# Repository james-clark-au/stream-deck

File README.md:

# James Neko's Stream Deck

I made my own 6-key macropad for streaming out of an old mechanical key 'switch tester' I had! In doing so, I designed and had my very first PCB manufactured!

There's code here for both Arduino C++ _(Using a Nano, and relying on a Perl [lazy-serial-daemon](https://github.com/james-clark-au/lazy-serial-daemon) plugin to respond to the keys)_ and CircuitPython for a TENSTAR RP2040 board that uses the Pro Micro form factor.

There's also some 3D printing files - one for the partial enclosure I adapted my switch tester with, one for a full housing for it.

## Configuration

Presuming you're using the RP2040 / CircuitPython version, you might want some help on configuring it.

### Getting the CIRCUITPY drive to show up

Because it's a bit annoying to see the virtual USB drive show up all the time, I configure mine to hide it by default. This is done by editing `boot.py` and changing the line `HIDE_CIRCUITPY_DRIVE = False` to `True`. When this is set to `True`, the device will only show up as two USB Serial ports and one USB HID (Keyboard/Mouse) device.

To get it to show up as a USB Mass Storage device again, so you can edit the onboard files, hold down Key 0 - the one closest to the cable - as you plug it in. You can let go once the drive shows up.

On the CIRCUITPY drive, the two files you want to edit are `boot.py` for the setting above, and `code.py` to change your keys' behaviours. If you're on a Microsoft system you _might_ need a text editor smarter than NOTEPAD.EXE.

### Editing the key mapping

At the top of `code.py` you should see the current behaviours assigned to each key. The example configuration defines two modes that can be switched between:-

```python
config_mode0 = {
  0: RadioButton(key=(Keycode.GUI, Keycode.Q), group=(0, 1, 2)),
  1: RadioButton(key=(Keycode.GUI, Keycode.R), group=(0, 1, 2)),
  2: RadioButton(key=(Keycode.GUI, Keycode.S), group=(0, 1, 2)),
  3: SimpleButton(key=Keycode.RIGHT_SHIFT),
  4: SpamButton(key=MouseLeft(), delay_ms=30),
  5: ModeSwitch(),
}
config_mode1 = {
  0: RadioButtonWithHold(key=(Keycode.CONTROL, Keycode.ALT, Keycode.SHIFT, Keycode.ONE), key_when_held="Hello", group=(0, 1)),
  1: RadioButtonWithHold(key=(Keycode.CONTROL, Keycode.ALT, Keycode.SHIFT, Keycode.TWO), key_when_held="World", group=(0, 1)),
  2: MomentaryButton(key_on=(Keycode.GUI, Keycode.V), key_off=(Keycode.GUI, Keycode.V), led_initial=False),
  3: ToggleButton(key_on=(Keycode.GUI, Keycode.V), key_off=(Keycode.GUI, Keycode.V), led_initial=True),
  4: ToggleButton(key_on="Bed goes up", key_off="Bed goes down"),
  5: ModeSwitch(),
}
```

Slightly below that, those 'modes' are loaded with the line:-
```
deck = StreamDeck(lazy, [config_mode0, config_mode1])
```

You'll only need to modify that if you want to play with lots of different modes; if you just want the same behaviour for each key all the time, edit `config_mode0` and don't worry about anything else.

You'll see that after each key number 0..5 is the name of a Python class and some parameters in parentheses. Don't forget the comma at the end. The parameters change depending on which class you use, but most take a `key=` parameter, or two `key_on=` and `key_off=` parameters. The key can be defined in a few different ways, but more on that later.

Here are the different behaviours you can use (defined in `Behaviours.py`):-

#### SimpleButton(key=, light_while_pressed=True)

The most basic. Sends the key down event for your `key` when you press the button, sends the key up event when you release it.

`light_while_pressed` controls what the LED should do - turn on as you press the button (True), or be on all the time (False).

#### ToggleButton(key_on=, key_off=, led_initial=False)

This button remembers whether it's 'on' or 'off', and starts 'off' (`led_initial`).

It does a quick tap of `key_on` when you turn it on, and a quick tap of `key_off` (which can be the same as `key_on`) when you push the button and turn the LED off.

You could use this for e.g. a 'mute mic' button, so the LED indicates whether you've muted or unmuted it -- assuming it starts in the right state. If you want it to accurately reflect your mute state, you'd need to write extra code for your computer.

#### MomentaryButton(key_on=, key_off=, led_initial=False)

This button defaults to being 'on' or 'off' (depending on how you set `led_initial`), and becomes 'off' or 'on' only while held down.

Like the ToggleButton, it does a quick tap of `key_on` when you turn it on, and a quick tap of `key_off` (which can be the same as `key_on`) when you push the button and turn the LED off.

You could use this for e.g. a 'push to talk' button, or a 'push to mute' button, so that it sends the keyboard shortcut to mute/unmute when you start holding it, and does the same thing when you release it.

#### RadioButton(key=, group=())

This button works a little like the SimpleButton, sending a key down event when you push it and sending the key release event when you let go. What changes here is the LED - it starts off, and when it is pushed it switches itself on - and all the other RadioButtons in the same group off.

You could use this for switching scenes in OBS - set the `key=` for each button to some complicated shortcut key you set in OBS, and now as you switch between them, the relevant light will stay on! Be sure to set the `group=` parameter to the numbers of each other RadioButton - e.g. the whole deck would be `group=(0,1,2,3,4,5)`.

You _can_ make the LEDs update if you switch scenes from clicking around in OBS, but that will require a program running on your computer to connect to OBS and the USB Serial Port the Deck exposes.

#### RadioButtonWithHold(key=, key_when_held=, group=())

Exactly the same as RadioButton, but:-

- It only taps the `key` when released, if you tap the button.
- If you hold the button down longer than a second, it instead taps the `key_when_held`, and begins flashing its LED instead of the LED being on continuously.

This way you get an extra second layer of possible radio buttons!

#### SpamButton(key=, light_while_pressed=True, delay_ms=20)

This button repeatedly taps the `key` for as long as you hold it.

#### ModeSwitch(prev=False, light_while_pressed=True)

This button switches to the next mode defined in the config, or if `prev=True`, the previous mode. The lights will briefly flash to indicate you've changed modes.

### Key definitions

There are multiple ways to specify what kind of key you want to simulate on a button push. Most of these reference `Keycode` definitions that come from the [adafruit_hid library](https://docs.circuitpython.org/projects/hid/en/latest/api.html#adafruit_hid.keycode.Keycode)

The simplest and most straightforward is a single key on your keyboard, such as `Keycode.RIGHT_SHIFT`, `Keycode.Q`, or `Keycode.F1`.

Most keyboard shortcuts you might want to use though, are going to be complex ctrl-alt-shift-super kind of chords that you wouldn't normally type - because you want to use some global shortcut that doesn't conflict with any application shortcuts. To do these, put a list of Keycode values in parentheses, modifiers first, then the key you want to trigger last. For example, `(Keycode.CONTROL, Keycode.ALT, Keycode.SHIFT, Keycode.ONE)`. The library refers to your Super or Command or MICROSOFT WINDOWS™ LOGO® key as `Keycode.GUI`.

If you want to get silly, you can also put a plain-text string for your `key=` value, such as `"Let's circle back and align our goals on this later."`. The code will type out the message.

Finally, it's possible to 'press' mouse buttons in place of keys. `MouseLeft()`, `MouseRight()` and `MouseMiddle()` are set up if you need to do this for some strange reason. Try it with `SpamButton`!

## Errata

When laying out the PCB, I decided to grab the closer A6 and A7 inputs for switches 4 and 5, but I forgot that the Arduino Nano _doesn't let you do digital input on those pins_. I ended up using bodge wires from A0 and A1 to A6 and A7 to let me still easily read the switch status.

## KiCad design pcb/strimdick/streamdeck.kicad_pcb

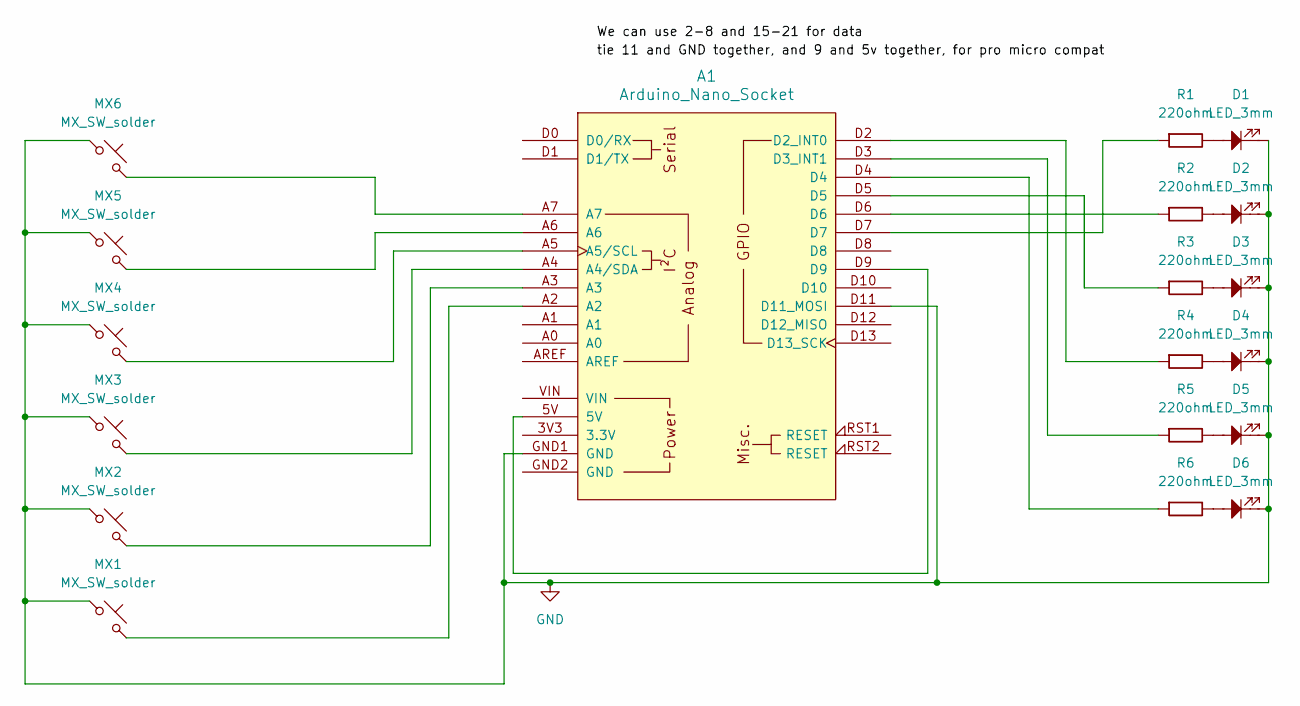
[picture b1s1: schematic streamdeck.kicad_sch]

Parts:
A1: Arduino_Nano_Socket
D1, D2, D3, D4, D5, D6: LED_3mm; LED_MX_3mm
MX1, MX2, MX3, MX4, MX5, MX6: MX_SW_solder; SW_MX_1u
R1, R2, R3, R4, R5, R6: 220ohm; R_Axial_DIN0207_L6.3mm_D2.5mm_P10.16mm_Horizontal

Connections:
GND: A1.D11 (D11_MOSI), A1.GND1 (GND), D1.1, D2.1, D3.1, D4.1, D5.1, D6.1, MX1.1, MX2.1, MX3.1, MX4.1, MX5.1, MX6.1
unnamed: A1.A4 (A4/SDA), MX3.2
unnamed: A1.A5 (A5/SCL), MX4.2
unnamed: A1.D2 (D2_INT0), R4.1
unnamed: A1.D3 (D3_INT1), R5.1
unnamed: A1.5V, A1.D9
unnamed: A1.A2, MX1.2
unnamed: A1.A3, MX2.2
unnamed: A1.A6, MX5.2
unnamed: A1.A7, MX6.2
unnamed: A1.D4, R6.1
unnamed: A1.D5, R3.1
unnamed: A1.D6, R2.1
unnamed: A1.D7, R1.1
unnamed: D1.2, R1.2
unnamed: D2.2, R2.2
unnamed: D3.2, R3.2
unnamed: D4.2, R4.2
unnamed: D5.2, R5.2
unnamed: D6.2, R6.2

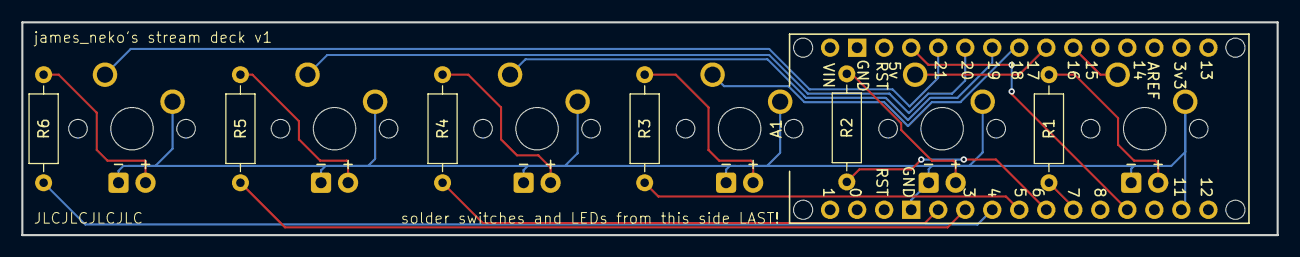
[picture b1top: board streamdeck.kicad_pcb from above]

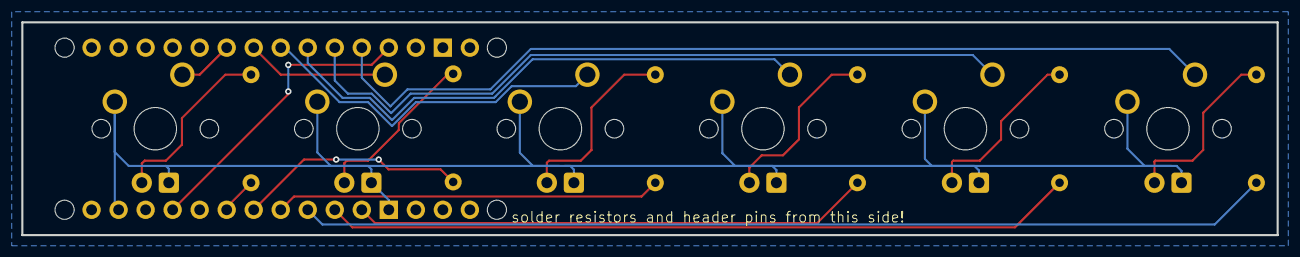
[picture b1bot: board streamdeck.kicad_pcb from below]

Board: 2 copper layers, 118.0 x 20.0 mm, 19 parts (12 on the bottom side), 20 nets.

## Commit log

2025-01-29 First bumbling
2025-01-29 Okay, got the schematic done, and a basic layout with things all stacked up, it's a bit tight
2025-01-29 Make Design Rules Checker happy
2025-01-29 Routing, some silkscreen instructions.
2025-01-29 trying this 'add fill' thing
2025-01-29 ignore gerber output
2025-01-29 Add JLC text
2025-02-12 Basic sketch.
2025-02-12 LED control
2025-02-13 Pinout diagram for Nano / Pro Micro
2025-02-15 3D model to add underneath my switch tester
2025-02-16 Use 0-based indexing
2025-02-16 First cut of saving to EEPROM.
2025-02-17 I dumb
2025-02-17 Add pin accessor.
2025-02-17 Fix saved script loading!
2025-02-17 Eyecatch
2025-02-17 PushButton and KEY command
2025-02-19 Create server code
2025-02-21 Initial extremely basic OBS client that can identify and listen for events
2025-02-21 Show scene selected from OBS!
2025-02-21 fuck yes, set OBS scene from StrimDick
2025-02-22 Make reconnects less spammy and more reliable
2025-02-22 fix: led sometimes cleared mistakenly
2025-02-22 Clear on exit
2025-02-22 Handle RequestResponse with Promises; sync OBS state on connect.
2025-02-22 Implement heartbeat to switch off if we lose connection to LSD
2025-03-14 pinout of this TENSTAR RP2040 board I'm using
2025-03-14 CircuitPy code
2025-03-14 LazySerial first cut
2025-03-15 Read and dispatch commands maybe
2025-03-15 remove debug
2025-03-15 BlinkyLed
2025-03-15 StrimDick main class
2025-03-15 Sketching out Behaviours
2025-03-18 Update pin
2025-03-18 Behaviour
2025-03-18 Behaviours, commands
2025-03-18 fukken python, man
2025-03-18 OHAI
2025-03-18 fix: dick
2025-03-18 Extend BlinkyLed to use as our main LED abstraction
2025-03-19 STL model for full housing
2025-03-20 add LED command
2025-03-20 add HEARTBEAT command
2025-03-20 Remove unneeded imports
2025-03-27 fix bloody index out of bounds error crashing the code
2025-03-27 fix: PushButton hold time
2025-03-27 fix: forgot to give the leds a tick
2025-03-27 Implement mode switching
2025-03-27 Add MomentaryButton
2025-03-29 Extend the USB hole down.
2025-03-29 Disable MIDI port
2025-03-31 Add mouse support
2025-03-31 Move helpers to their own file. Create SpamButton.
2025-03-31 Tweak delay
2025-04-10 forgot to add...
2025-04-10 Fix some error handling
2025-04-11 Extract a Protocol module
2025-04-11 whups
2025-04-14 REAMDE
2025-04-23 cleanup
